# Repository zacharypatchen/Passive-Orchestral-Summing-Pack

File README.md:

# Passive-Orchestral-Summing-Pack

Video describing system: https://youtu.be/avfMIS6j09w?si=Rws9fPx7UGtwEoFt
<br>
The Summing Pack is a passive device used to minimize mic inputs for an orchestral recording. Eight mic lines can be summed down to one, improving mixing board input efficiency. Note, this is passive so it requires a mic pre with plenty of gain & high SINAD dB.

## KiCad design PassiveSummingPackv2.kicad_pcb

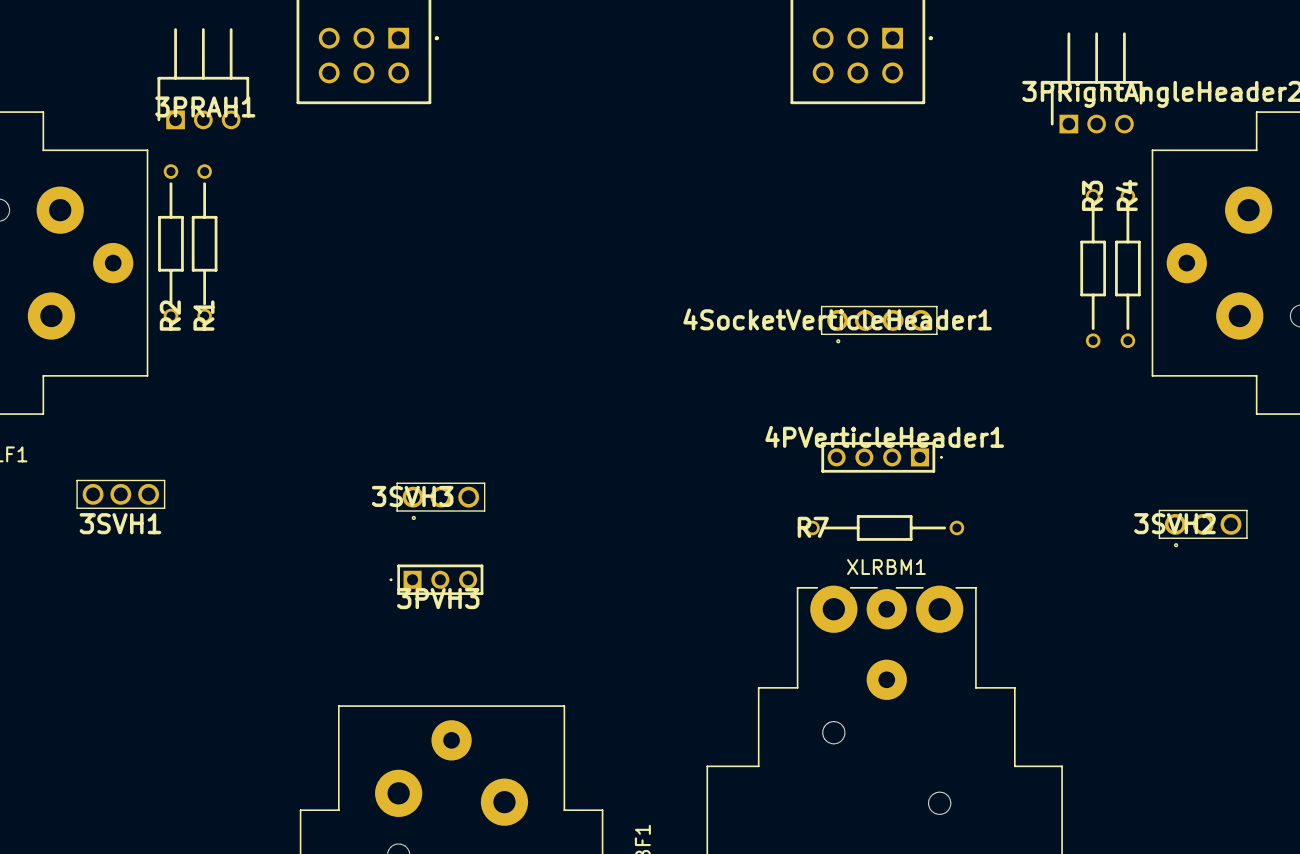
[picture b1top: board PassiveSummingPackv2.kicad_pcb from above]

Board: 2 copper layers, 19 parts (0 on the bottom side), 25 nets, no tracks yet.

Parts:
3PRAH1, 3PRightAngleHeader2: M22-2030305; HDRRA3W50P0X200_1X3_600X150X200P
3PVH3: 2MM-HB-S03-VT-02-H-TB; 2MMHBS03VT02HTB
3SVH1, 3SVH2, 3SVH3: SQT-103-01-F-S; SQT-103-01-XX-S
4PVerticleHeader1: 2MM-HB-S04-VT-02-H-TB; 2MMHBS04VT02HTB
4SocketVerticleHeader1: SQT-104-01-F-S; SQT-104-01-XX-S
R1, R2, R3, R4: 4.7kOHM; RESAD1041W46L381D165
R7: 330ohm; RESAD1041W46L381D165
VR1: Input1Pot1; PTD9021015KA102
VR2: Input2Pot2; PTD9021015KA102
XLRBF1: NC3FAH; Jack_XLR_Neutrik_NC3FAH_Horizontal
XLRBM1: NC3MAH; Jack_XLR_Neutrik_NC3MAH_Horizontal
XLRLF1: NC3FAH; Jack_XLR_Neutrik_NC3FAH_Horizontal
XLRRF1: NC3FAH; Jack_XLR_Neutrik_NC3FAH_Horizontal

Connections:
unnamed: 3PRAH1.1, XLRLF1.1
unnamed: 3PRAH1.2, R1.2
unnamed: 3PRAH1.3, R2.2
unnamed: 3PRightAngleHeader2.1, XLRRF1.1
unnamed: 3PRightAngleHeader2.2, R3.1
unnamed: 3PRightAngleHeader2.3, R4.1
unnamed: 3PVH3.1, XLRBF1.1
unnamed: 3PVH3.2, XLRBF1.2
unnamed: 3PVH3.3, XLRBF1.3
unnamed: 3SVH1.1, 3SVH2.1, 3SVH3.1, 4SocketVerticleHeader1.1
unnamed: 4PVerticleHeader1.1, XLRBM1.1
unnamed: 4PVerticleHeader1.2, R7.1, XLRBM1.2
unnamed: 4PVerticleHeader1.3, R7.2, XLRBM1.3
unnamed: 4PVerticleHeader1.4, XLRBM1.G
unnamed: R1.1, XLRLF1.2
unnamed: R2.1, XLRLF1.3
unnamed: R3.2, XLRRF1.2
unnamed: R4.2, XLRRF1.3
unnamed: 4SocketVerticleHeader1.4, VR1.R11 (CCW_1), VR1.R21 (CCW_2), VR2.R11 (CCW_1), VR2.R21 (CCW_2)
unnamed: 3SVH1.3, VR1.R13 (CW_1)
unnamed: 3SVH1.2, VR1.R23 (CW_2)
unnamed: 3SVH3.3, 4SocketVerticleHeader1.3, VR1.R12 (WIPER_1), VR2.R22 (WIPER_2)
unnamed: 3SVH3.2, 4SocketVerticleHeader1.2, VR1.R22 (WIPER_2), VR2.R12 (WIPER_1)
unnamed: 3SVH2.2, VR2.R13 (CW_1)
unnamed: 3SVH2.3, VR2.R23 (CW_2)

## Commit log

2026-02-25 init commit
2026-02-25 Enhance README with image and video description
    Added image and video link to README for better context.
2026-02-25 Update README with SINAD dB clarification
    Clarified the description of the Summing Pack by adding 'dB' to the SINAD reference.
2026-02-25 Fix grammatical error in README description
2026-02-26 Update description of Summing Pack in README
    Clarified the gain requirement for the mic pre.
2026-03-02 Add MIT License to the project
